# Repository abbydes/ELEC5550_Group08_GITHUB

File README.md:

# ELEC5550 Group08 GITHUB Repository

## USB Host and Device Function
The USB host and device functionality is based on the ESP-IDF library which can be found [here](https://github.com/espressif/esp-idf?tab=readme-ov-file). 
The project requires an ESP32-S3 to host for both [USB HID](https://github.com/espressif/esp-idf/tree/master/examples/peripherals/usb/host/hid) and [USB MSC](https://github.com/espressif/esp-idf/tree/master/examples/peripherals/usb/host/msc) devices while another ESP32-S3 acts as a [USB HID](https://github.com/espressif/esp-idf/tree/master/examples/peripherals/usb/device/tusb_hid) and/or [USB MSC](https://github.com/espressif/esp-idf/tree/master/examples/peripherals/usb/device/tusb_msc) device to an external laptop for system transparency.

Code regarding the USB host & device functionality can be found in the USB folder.

## Handshake Protocol
The project outlines the use of two modules that can communicate with one another through free-space optical communication. The handshake protocol is the method used to establish the laser connection in the case of initialisation and will be used if the laser is interrupted and connection must be reestablished. 

Code regarding the initial Handshake protocol can be found in the HANDSHAKE folder.
NOTE: handshake code in folder was implemented into MSC and updated

## USB MSC Virtual Storage
A virtual storage system will be required on the module connected to the host laptop as the USB MSC protocol may be too strenuous to implement over serial laser communication. As such, the contents of the USB file will be transferred over the laser and reconstructed in the virtual storage.

Code regarding the Virtual Storage can be found in the VIRTUAL_STORAGE folder.

## Error Correction
For the data to be transferred correctly between modules via the laser a method of error correction must be implemented. The type of error correction that will be implemented is a combination of cyclical redundancy check (CRC) checksum with stop-and-wait Automatic Repeat request (ARQ).

Code regarding the initial Error Correction can be found in the ERROR_CORRECTION folder.
NOTE: error correction in folder was implemented into HID and MSC and updated

## USB HID Encoding/Decoding
The project specifies the connection of a mouse or keyboard into a module which then encodes the HID data, transfers it over the laser, decodes it and provides it to the host laptop.

Code regarding HID Encoding/decoding can be found in the HID folder.

## USB MSC Encoding/Decoding
The project specifies the connection of a USB flashdrive into a module which then encodes the MSC data, transfers it over the laser, decodes it and provides it to the host laptop.

Code regarding MSC Encoding/decoding can be found in the MSC folder alongside descriptions for each code version and code flow diagrams.

## ESP32 Prototyping
This project includes the creation of both hardware and software. Rudimentary pieces of code were used to verify hardware design using the ESP32-S3 as a stepping stone to PCB design.

Code regarding ESP32-S3 hardware verification can be found in the ESP32 PROTOTYPING folder.

## PCB Prototyping
Similary to the ESP32-S3 prototype testing, rudimentary pieces of code were required to verify the PCBs functionality in comparison to the ESP32-S3 prototype it was based on.

Code regarding PCB hardware verification can be found in the PCB PROTOTYPING folder.

The PCB prototyping folder also includes the KICAD design documents which are located in the KICAD DESIGN folder under PCB Prototyping

## File Management
All files are to be uploaded to their respective folders. New file versions to be created each week to allow for proper version control.

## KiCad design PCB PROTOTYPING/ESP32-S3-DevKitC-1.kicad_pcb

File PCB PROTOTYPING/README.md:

This folder contains the code used to verify hardware prototyping and the KiCad design files for the PCB

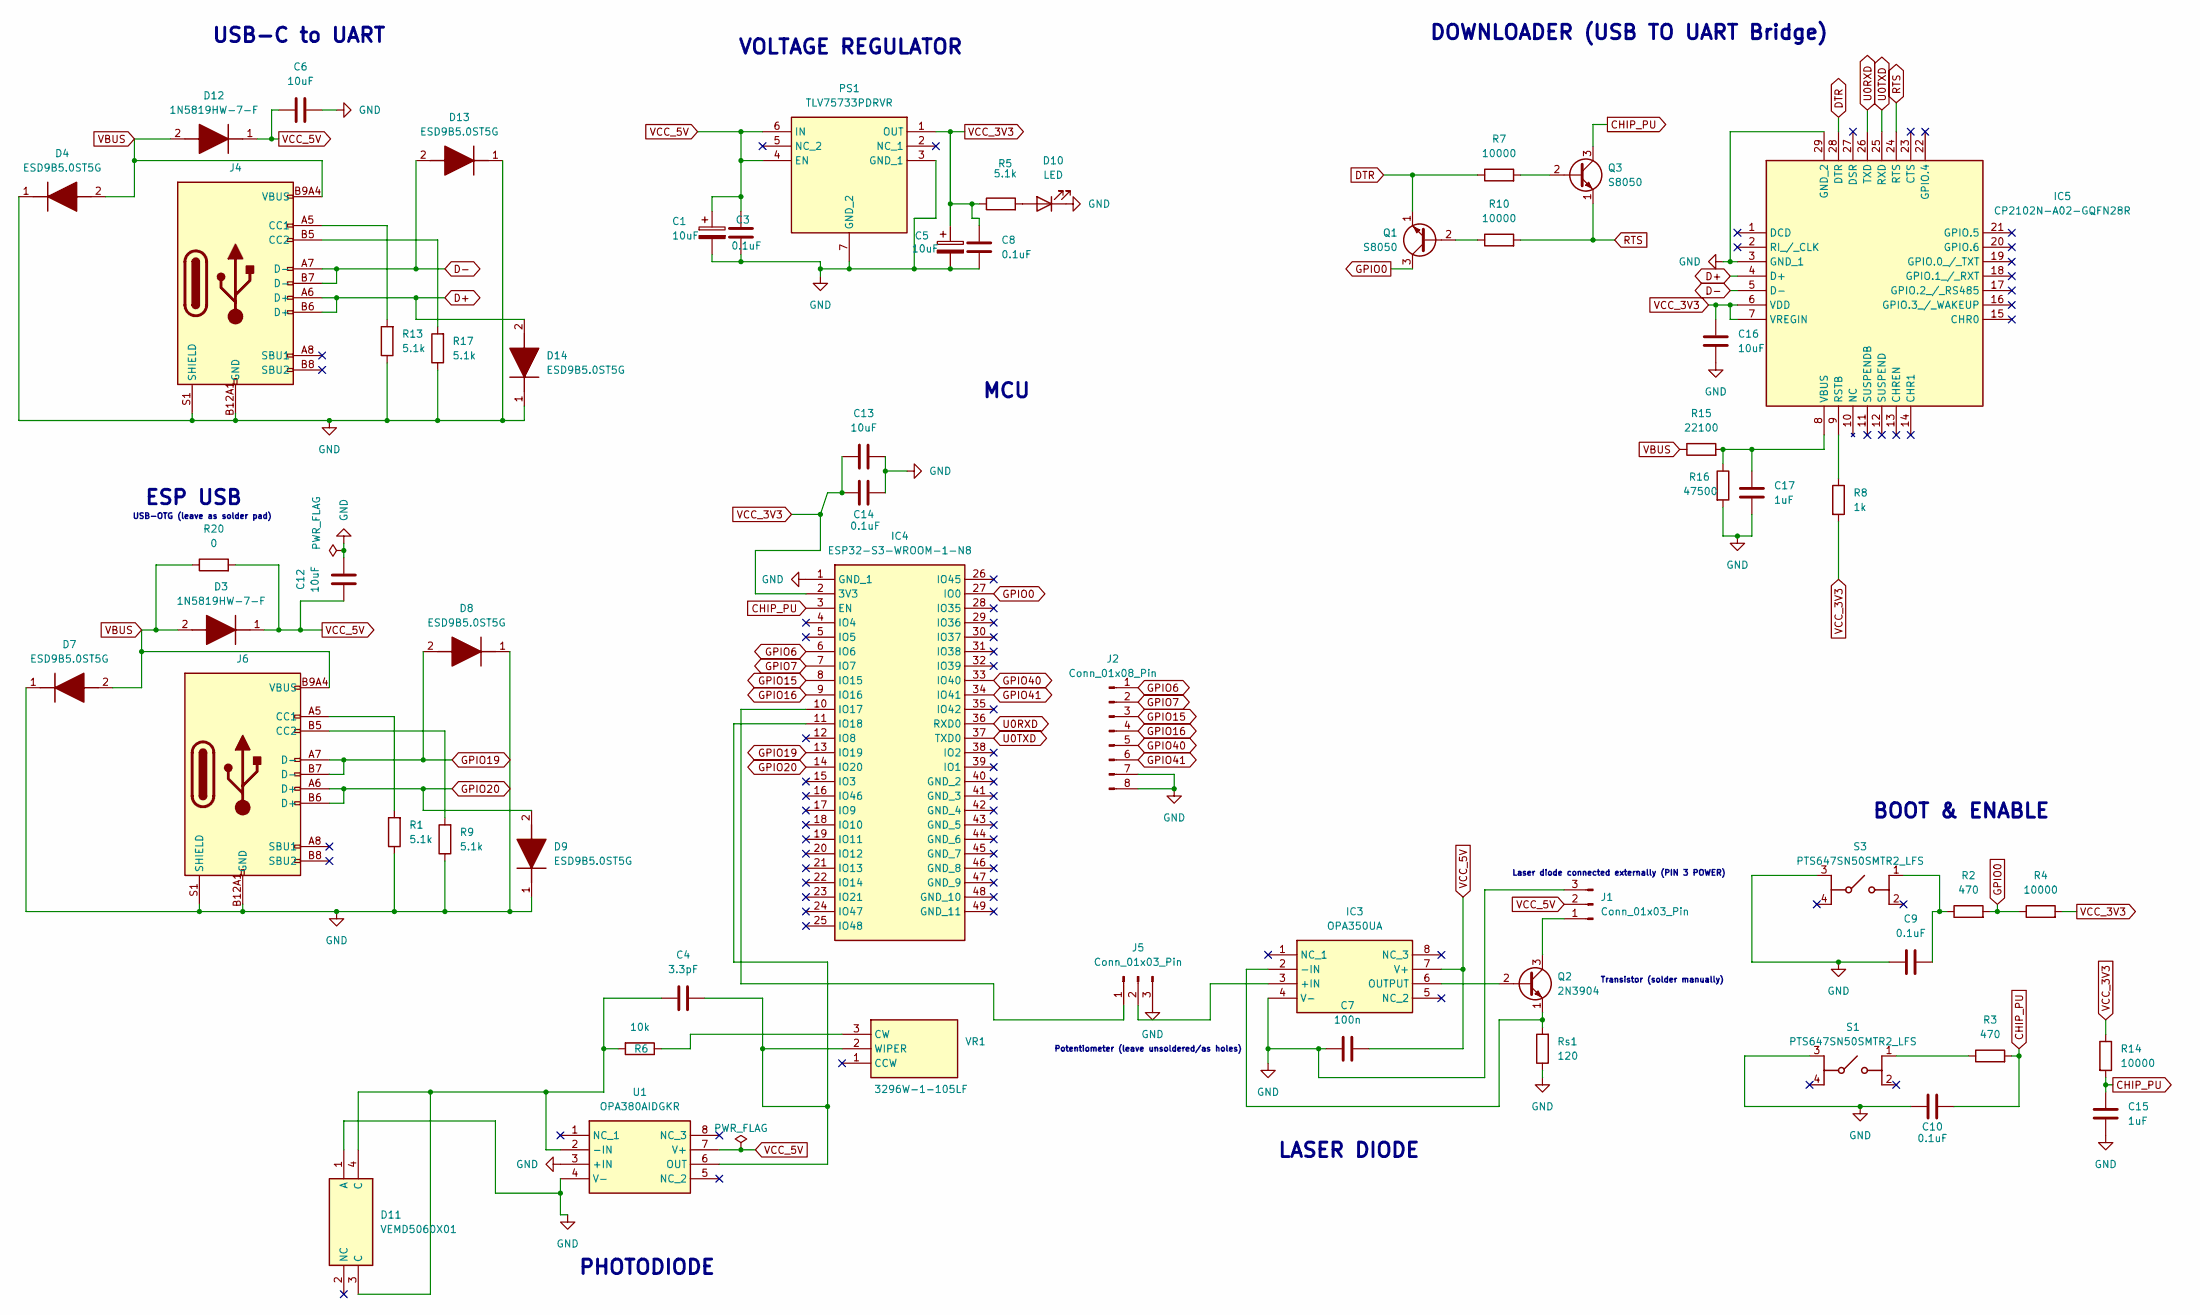
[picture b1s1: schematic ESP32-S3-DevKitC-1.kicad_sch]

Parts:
C1, C5, C6, C12, C13, C16: 10uF; C_0805_2012Metric
C3, C8, C9, C10, C14: 0.1uF; C_0805_2012Metric
C4: 3.3pF; C_0805_2012Metric
C7: 100n; C_0805_2012Metric
C15, C17: 1uF; C_0805_2012Metric
D3, D12: 1N5819HW-7-F; SOD3716X145N; Mouser Part Number 621-1N5819HW-F
D4, D7, D8, D9, D13, D14: ESD9B5.0ST5G; SODFL1006X40N; Mouser Part Number 863-ESD9B5.0ST5G
D10: LED; LED_0805_2012Metric
D11: VEMD5060X01; Mouser Part Number 78-VEMD5060X01
IC3: OPA350UA; SOIC127P600X175-8N; Mouser Part Number 595-OPA350UA
IC4: ESP32-S3-WROOM-1-N8; ESP32S3WROOM1N8R2; Mouser Part Number 356-ESP32-S3WROOM1N8
IC5: CP2102N-A02-GQFN28R; QFN50P500X500X80-29N-D; Mouser Part Number 634-CP2102NA02QFN28R
J1, J5: Conn_01x03_Pin; PinHeader_1x03_P2.54mm_Vertical
J2: Conn_01x08_Pin; PinHeader_1x08_P2.54mm_Vertical
J4, J6: Connector, USB-TYPE-C-16P; TYPE-C-SMD_HX-TYPE-C-16PIN; LCSC C2927039
PS1: TLV75733PDRVR; SON65P200X200X80-7N; Mouser Part Number 595-TLV75733PDRVR
Q1, Q3: S8050; TO-92_Inline
Q2: 2N3904; TO-92_Inline
R1, R5, R9, R13, R17: 5.1k; R_0805_2012Metric
R2, R3: 470; R_0805_2012Metric
R4, R7, R10, R14: 10000; R_0805_2012Metric
R6: 10k; R_0805_2012Metric
R8: 1k; R_0805_2012Metric
R15: 22100; R_0805_2012Metric
R16: 47500; R_0805_2012Metric
R20: 0; R_0805_2012Metric
Rs1: 120; R_0805_2012Metric
S1, S3: PTS647SN50SMTR2_LFS; PTS647SK50SMTR2LFS; Manufacturer_Part_Number PTS647SN50SMTR2 LFS
U1: OPA380AIDGKR; SOP65P490X110-8N; Mouser Part Number 595-OPA380AIDGKR
VR1: 3296W-1-105LF; 3296W1503LF; Mouser Part Number 652-3296W-1-105LF

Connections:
CHIP_PU: C10.2, C15.2, IC4.3 (EN), Q3.3 (C), R3.2, R14.2
D+: D14.2 (A), IC5.4 (D+), J4.A6 (D+), J4.B6 (D+)
D-: D13.2 (A), IC5.5 (D-), J4.A7 (D-), J4.B7 (D-)
DTR: IC5.28 (DTR), Q1.1 (E), R7.1
GND: C1.2, C3.2, C5.2, C6.2, C7.2, C8.2, C9.1, C10.1, C12.2, C13.2, C14.2, C15.1, C16.1, C17.1, D4.1 (K), D7.1 (K), D8.1 (K), D9.1 (K), D10.1 (K), D11.1 (A), D13.1 (K), D14.1 (K), IC3.4 (V-), IC4.1 (GND_1), IC5.3 (GND_1), IC5.29 (GND_2), J1.3, J2.7, J2.8, J4.A12B1 (GND), J4.B12A1 (GND), J4.S1 (SHIELD), J5.3, J6.A12B1 (GND), J6.B12A1 (GND), J6.S1 (SHIELD), PS1.3 (GND_1), PS1.7 (GND_2), R1.1, R9.1, R13.1, R16.2, R17.1, Rs1.1, S1.3 (COM_1), S3.3 (COM_1), U1.3 (+IN), U1.4 (V-)
GPIO0: IC4.27 (IO0), Q1.3 (C), R2.2, R4.1
GPIO6: IC4.6 (IO6), J2.1
GPIO7: IC4.7 (IO7), J2.2
GPIO15: IC4.8 (IO15), J2.3
GPIO16: IC4.9 (IO16), J2.4
GPIO19: D8.2 (A), IC4.13 (IO19), J6.A7 (D-), J6.B7 (D-)
GPIO20: D9.2 (A), IC4.14 (IO20), J6.A6 (D+), J6.B6 (D+)
GPIO40: IC4.33 (IO40), J2.5
GPIO41: IC4.34 (IO41), J2.6
unnamed: D10.2 (A), R5.2
unnamed: IC3.3 (+IN), J5.2
unnamed: IC3.2 (-IN), Q2.1 (E), Rs1.2
unnamed: IC3.6 (OUTPUT), Q2.2 (B)
unnamed: IC4.10 (IO17), J5.1
unnamed: C4.1, IC4.11 (IO18), U1.6 (OUT), VR1.2 (WIPER)
unnamed: IC5.9 (RSTB), R8.1
unnamed: C17.2, IC5.8 (VBUS), R15.2, R16.1
unnamed: J1.1, Q2.3 (C)
unnamed: J4.A5 (CC1), R13.2
unnamed: J4.B5 (CC2), R17.2
unnamed: J6.A5 (CC1), R1.2
unnamed: J6.B5 (CC2), R9.2
unnamed: Q1.2 (B), R10.1
unnamed: Q3.2 (B), R7.2
unnamed: R3.1, S1.1 (NO_1)
unnamed: C9.2, R2.1, S3.1 (NO_1)
unnamed: C4.2, D11.3 (C), D11.4 (C), R6.2, U1.2 (-IN)
unnamed: R6.1, VR1.3 (CW)
RTS: IC5.24 (RTS), Q3.1 (E), R10.2
U0RXD: IC4.36 (RXD0), IC5.26 (TXD)
U0TXD: IC4.37 (TXD0), IC5.25 (RXD)
VBUS: D3.2 (A), D4.2 (A), D7.2 (A), D12.2 (A), J4.A9B4 (VBUS), J4.B9A4 (VBUS), J6.A9B4 (VBUS), J6.B9A4 (VBUS), R15.1, R20.1
VCC_3V3: C5.1, C8.1, C13.1, C14.1, C16.2, IC4.2 (3V3), IC5.6 (VDD), IC5.7 (VREGIN), PS1.1 (OUT), R4.2, R5.1, R8.2, R14.1
VCC_5V: C1.1, C3.1, C6.1, C7.1, C12.1, D3.1 (K), D12.1 (K), IC3.7 (V+), J1.2, PS1.4 (EN), PS1.6 (IN), R20.2, U1.7 (V+)

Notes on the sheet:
LASER DIODE
MCU
BOOT & ENABLE
USB-OTG (leave as solder pad)
PHOTODIODE
Potentiometer (leave unsoldered/as holes)
USB-C to UART
Laser diode connected externally (PIN 3 POWER)
VOLTAGE REGULATOR
Transistor (solder manually)
ESP USB
DOWNLOADER (USB TO UART Bridge)

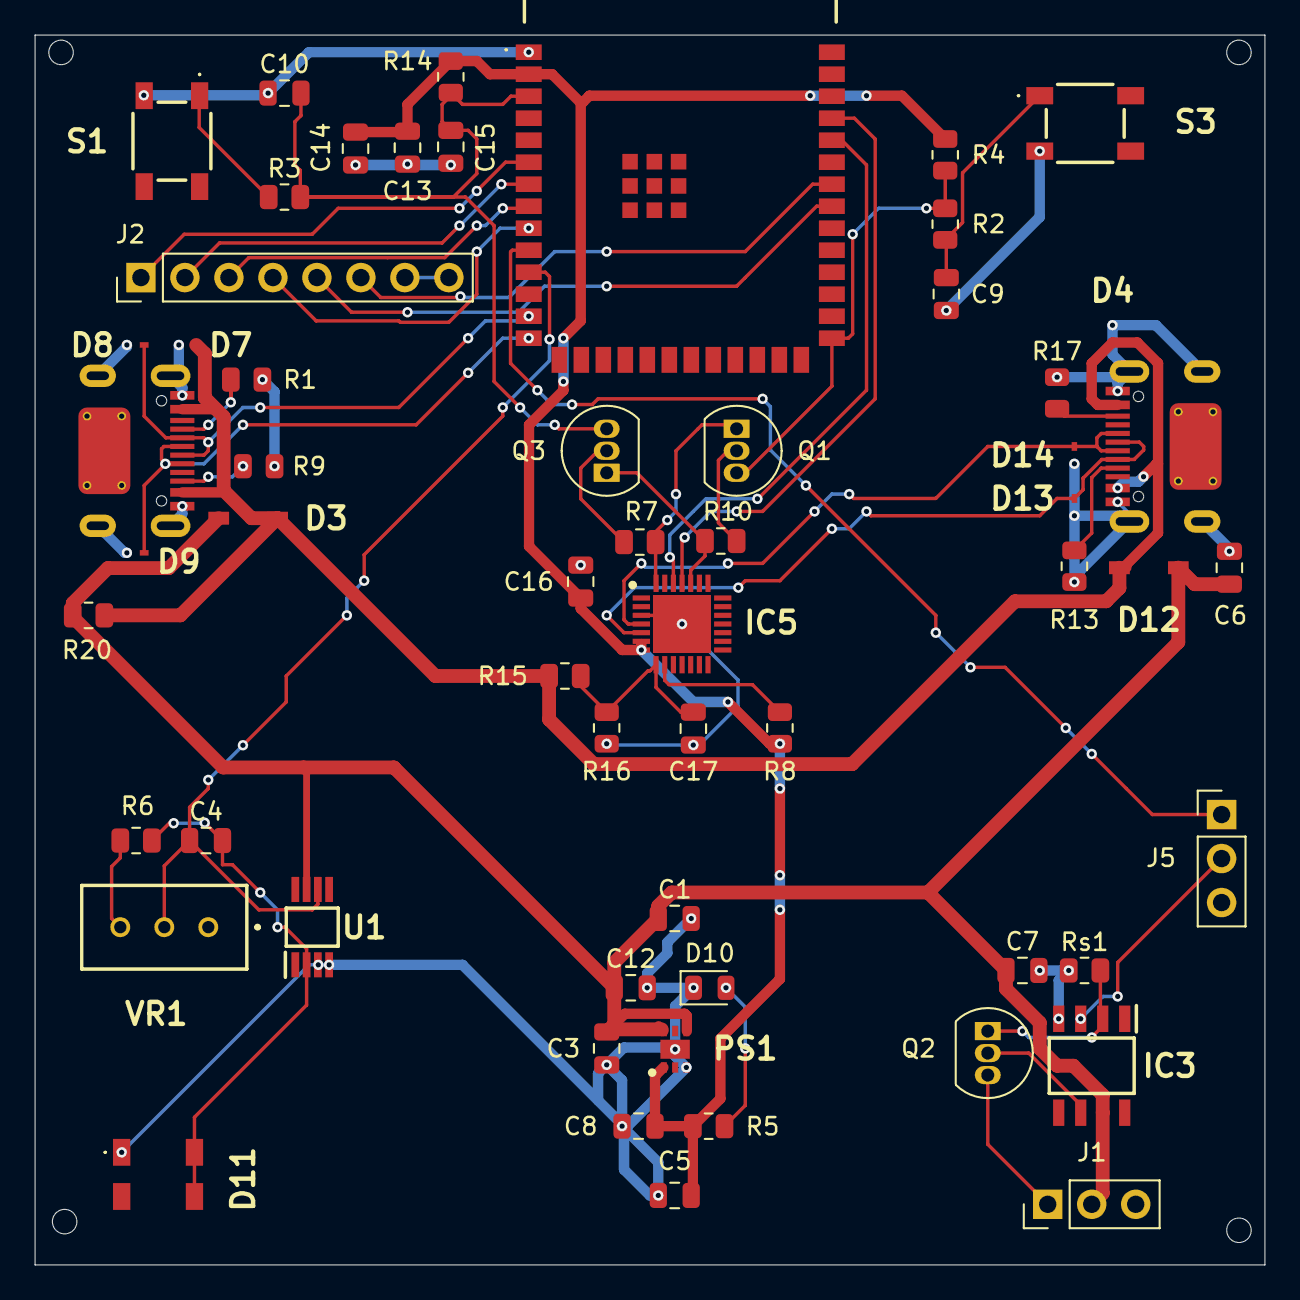
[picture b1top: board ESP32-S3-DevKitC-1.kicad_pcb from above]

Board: 2 copper layers, 71.0 x 71.0 mm, 58 parts (0 on the bottom side), 39 nets.

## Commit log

2025-08-25 Create USB
2025-08-25 Update and rename HIDDecoding to HIDDecoding_V01
2025-08-25 Update and rename HIDEncoding to HIDEncoding_V01
2025-08-25 Update and rename SimplifiedHIDHost to SimplifiedHIDHost_V01
2025-08-25 Update and rename USB/SimplifiedHIDHost_V01 to USB/Archive/SimplifiedHIDHost_V01
2025-08-25 Update and rename HID/HIDDecoding_V01 to HID/ARCHIVE/HIDDecoding_V01
2025-08-25 Update and rename HID/HIDEncoding_V01 to HID/ARCHIVE/HIDEncoding_V01
2025-09-03 Rename host_main.c to host_main_V1.c
2025-09-03 Rename dev_main.c to dev_main_V1.c
2025-09-07 Add files via upload
    To test TinyUSB functionality. This will make a storage drive on the target computer.
2025-09-09 Rename MSC/dev_main_V1.c to MSC/ARCHIVE/dev_main_V1.c
2025-09-09 Rename MSC/host_main_V1.c to MSC/ARCHIVE/host_main_V1.c
2025-09-10 Create dev_main_V2
2025-09-10 Create host_main_V2
2025-09-11 Rename MSC/dev_main_V2 to MSC/ARCHIVE/dev_main_V2
2025-09-11 Rename MSC/host_main_V2 to MSC/ARCHIVE/host_main_V2
2025-09-11 PROTOTYPE folder renamed
2025-09-11 Create PCB PROTOTYPING
2025-09-11 Create USB Examples
2025-09-11 Rename USB Examples to MSC/USB Examples
2025-09-11 Create host
2025-09-11 MSC host file name changed to host_main_V3
2025-09-16 Rename MSC/host_main_V3/README.md to MSC/ARCHIVE/host_main_V3/README.md
2025-09-16 Rename MSC/host_main_V3/c_cpp_properties.json to MSC/ARCHIVE/host_main_V3/c_cpp_properties.json
2025-09-16 Create msc_example_main
2025-09-16 Update msc_example_main
2025-09-16 dev_main_V3 moved to archive
2025-09-16 Create tusb_msc_main
2025-09-17 Create receiverdrive
2025-09-18 dev_main_v4 moved to ARCHIVE
2025-09-18 host_main_v4 moved to ARCHIVE
2025-09-23 Add files via upload
    added released keys (delay)
2025-09-23 Add files via upload
    updated release keys to read previous state
2025-09-23 Create ledpatch
2025-09-25 dev_main_V5 moved to ARCHIVE
2025-09-26 Rename ledpatch to ledpatch.c
2025-09-26 Create HIDhid_device_v5_LED
2025-09-26 Rename HIDhid_device_v5_LED to HID/HIDhid_device_v5_LED
2025-09-26 Update HIDhid_device_v5_LED
2025-09-29 Update and rename HIDhid_device_v5_LED to HIDhid_device_v5_LED.c
    Fixed issues with LED. Correctly flashes
2025-09-29 Rename HID/hid_device_v6.c to HID/ARCHIVE/hid_device_v6.c
2025-09-30 Create HID_device_v8_TBD
2025-10-01 Rename HID/hid_device_v7.c to HID/ARCHIVE/hid_device_v7.c
2025-10-02 Moved host_main_V5 and dev_main_V6 to ARCHIVE
2025-10-03 Create UART_bridge_B_V1
2025-10-03 Create UART_bridge_A_V1
2025-10-03 Rename HID/HID_device_v8_TBD to HID/ARCHIVE/hid_device_v8
2025-10-03 Rename HID_device_v9_LED.c to hid_device_v9_LED.c
2025-10-03 Rename hid_device_v9_LED.c to hid_device_v10.c
2025-10-03 Rename HID/hid_keyboard_test.c to HID/ARCHIVE/hid_v2.c
2025-10-03 Rename HID/HIDhid_device_v5_LED.c to HID/ARCHIVE/hid_device_v5_LED.c
2025-10-03 Rename hid_device_v8 to hid_device_v8.c
2025-10-05 dev_main_V7 and host_main_V6 moved to ARCHIVE
2025-10-10 Update UART_bridge_B_V1
2025-10-14 Rename hid_host_v7.c to HID/ARCHIVE/hid_host_v7.c
2025-10-14 Rename hid_device_v7.c to HID/ARCHIVE/hid_device_v7a.c
2025-10-24 Moved outdated code in MSC to MSC/ARCHIVE
2025-10-24 Add README with modifications for USB-MSC example
    This README outlines modifications made to the USB-MSC device example, including files to verify and modify for successful builds.
2025-10-24 Rename HID/hid_device_v9.c to HID/ARCHIVE/hid_device_v9.c
2025-10-24 renamed host_main_v8 to host_main_V8
2025-10-24 renaming host_main and dev_main in MSC
2025-10-27 Implement USB MSC host functionality for Board B
    This commit adds a comprehensive implementation for Board B as a USB MSC host, including handshake protocols, UART configuration, and handling of READ10 and WRITE10 SCSI commands.
2025-10-27 Refactor msc_example_main.c for clarity and structure
2025-10-27 Rename hid_device_v10.c to hid_device_LED.c
2025-10-27 Rename HID/ARCHIVE/hid_device_v9.c to HID/hid_device_v9.c
2025-10-27 Remove hid_device_LED.c from the HID archive
2025-10-27 Remove hid_host_esp-idf.c from HID directory
2025-10-27 README.md
2025-10-27 Create KiCAD PCB
